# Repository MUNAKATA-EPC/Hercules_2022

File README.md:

# Hercules_2022

ヘラクレス2022シーズンのソースコード、基板データを公開しています。

詳しくはWikiを参照。

## 運用方針

- 大きな変更をするときはブランチを絶対に別途作成しましょう
- 小さな変更(スペルミスやコメント修正程度)ならどんどんmainブランチに突っ込んでもまあ構わないでしょう
- 余裕があったら変更した内容をコメントしてくれると助かります

## コードに関して

- 各プロジェクトフォルダの命名規則は「hogehoge(プロジェクト名)-teensy40(開発環境名)」となっていますが、一部試験用に作ったものに関しては、この命名規則が守られておりません...ごめんなさい。
- プロジェクトフォルダ内の「src」フォルダ内にmain.cpp(一部プロジェクトは名称が異なります)、「lib」フォルダ内に各種ライブラリ、「include」フォルダ内にサブプログラムが入っています。
- 一部PlatformIOからダウンロードしているライブラリが含まれているため、基本は「VSCode + PlatformIO」の組み合わせでご覧ください。

## 回路に関して

- 使用する設計ソフトにKiCad5と6が混在しています。
- ライブラリについてはLibraryフォルダを相対パスで参照しています。
- 発注は主にJLCPCBを使用します。

## 開発環境に関して

- VSCodeの拡張機能のPlatformIOを使用しTeensy 4.0とSeeeduino XIAOに書き込んでいます。
- 弊チームにはMacユーザーがいないため、Windows環境での開発を想定しております。Macをお使いの皆様、何か問題が生じても対応はできません。予めご了承ください。

## ライセンスに関して

- すべてのコード、基板データに関するライセンスはMITにしていますが、ライブラリ等のライセンスはそのライブラリごとのライセンスに従ってください。

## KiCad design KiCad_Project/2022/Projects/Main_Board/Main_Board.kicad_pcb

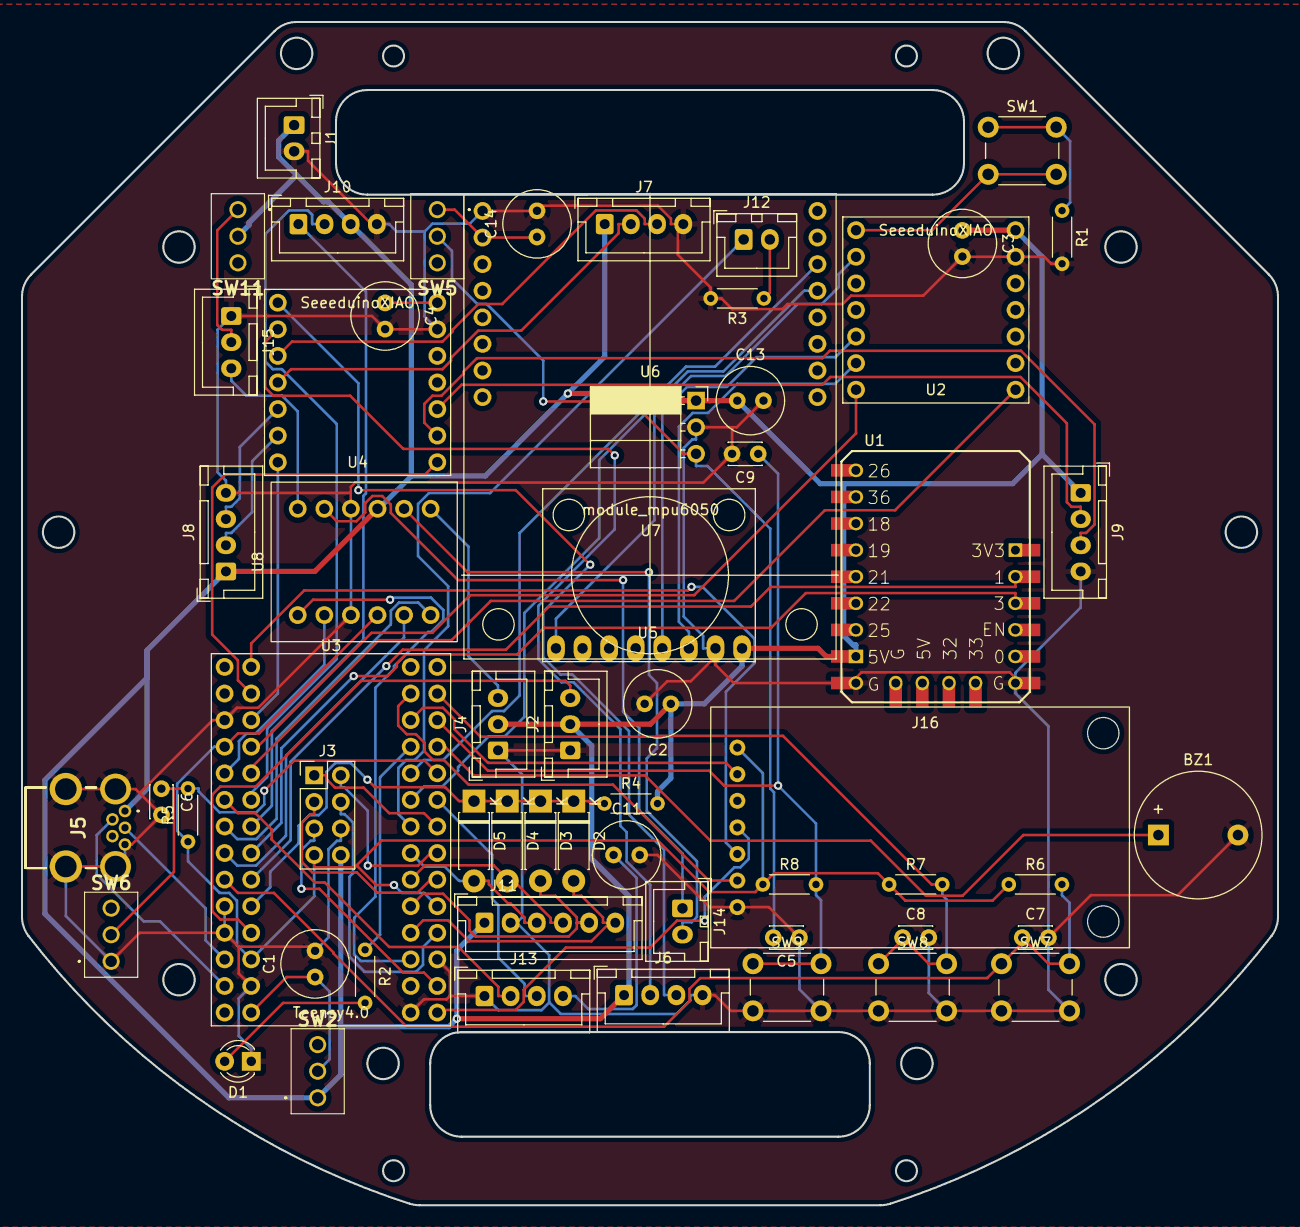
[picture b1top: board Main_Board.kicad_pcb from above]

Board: 2 copper layers, 120.0 x 113.0 mm, 58 parts (0 on the bottom side), 68 nets.

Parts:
BZ1: Buzzer; Buzzer_12x9.5RM7.6
C1, C2, C3, C4, C11, C13, C14: C_Small; C_Radial_D6.3mm_H11.0mm_P2.50mm
C5, C6, C7, C8, C9: C; C_Disc_D3.0mm_W2.0mm_P2.50mm
D1: LED; LED_D3.0mm_Clear
D2, D3, D4, D5: D; D_DO-41_SOD81_P7.62mm_Horizontal
J1, J12, J14: Conn_01x02; JST_XH_B2B-XH-A_1x02_P2.50mm_Vertical
J2, J4, J15: Conn_01x03; JST_XH_B3B-XH-A_1x03_P2.50mm_Vertical
J3: Conn_01x08; PinHeader_2x04_P2.54mm_Vertical
J5: USB_B_Micro; MUSB5BF01AS
J6, J7, J8, J9, J10, J13: Conn_01x04; JST_XH_B4B-XH-A_1x04_P2.50mm_Vertical
J11: Conn_01x06; JST_XH_B6B-XH-A_1x06_P2.50mm_Vertical
J16: Conn_01x07; LCD
R1, R2, R3, R4, R5, R6, R7, R8: R; R_Axial_DIN0204_L3.6mm_D1.6mm_P5.08mm_Horizontal
SW1, SW7, SW8, SW9: SW_Push; SW_PUSH_6mm_H5mm
SW2, SW5, SW11: SW_SPST; toggleswitch
SW6: SW_DIP_x01; toggleswitch
U1: Stamp_Pico; StampPico_template
U2, U4: SeeeduinoXIAO; seeeduinoXIAO
U3: Teensy4.0; Teensy
U5: OpenMV
U6: LF33_TO252; PinSocket_1x03_P2.54mm_Horizontal
U7: module_mpu6050; MPU6050
U8: Akizuki_Logiv_Level_converter; Akizuki_Logic_Level_converter

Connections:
+3V3: J3.7, J16.1, R5.1, R6.1, R7.1, R8.1, U3.31 (3V3), U8.9 (LV)
+5V: C2.1, C3.1, C13.1, J1.1, J2.2, J3.8, J4.2, J5.1 (VBUS), J6.1, J7.1, J8.1, J9.1, J10.3, J11.1, R4.2, SW2.1 (A), SW11.2 (B), U1.8 (5V), U2.14 (5V), U6.1 (VI), U7.1 (VCC), U8.4 (HV)
/Kicker: J12.1, U3.8 (6_OUT1D)
CS: J16.2, U3.12 (10_CS_MQSR)
GND: BZ1.2 (+), C1.2, C2.2, C3.2, C4.2, C5.1, C6.2, C7.2, C8.2, C9.2, C11.2, C13.2, C14.2, D1.1 (K), J1.2, J2.1, J3.6, J4.1, J5.5 (GND), J6.4, J7.4, J8.4, J9.4, J10.4, J11.2, J13.1, J15.1, J16.7, R1.2, R3.2, SW6.1, SW7.2, SW8.2, SW9.2, U1.9 (GND), U1.14 (GND), U2.13 (GND), U3.1 (GND), U4.13 (GND), U5.1 (GND), U6.2 (GND), U7.2 (GND), U8.3 (GND), U8.10 (GND)
Intterapt: D2.1 (K), D3.1 (K), D4.1 (K), D5.1 (K), R4.1, U3.29 (22_A8_CTX1)
MOSI: J16.6, U3.13 (11_MOSI_CTX1)
NeoPixel: U3.37 (26_A12_MOSI1), U8.7 (LV4)
unnamed: BZ1.1 (-), U3.44 (33_MCLK2)
unnamed: C1.1, SW2.2 (B), U3.33 (VIN)
unnamed: C4.1, U4.14 (5V)
unnamed: C5.2, SW5.2 (B), U6.3 (VO)
unnamed: C11.1, J13.4
unnamed: C14.1, SW5.1 (A), U5.2 (VIN)
unnamed: D1.2 (A), R2.2
unnamed: D2.2 (A), J11.6, U3.4 (2_OUT2)
unnamed: D3.2 (A), J11.5, U3.5 (3_LRCLK2)
unnamed: D4.2 (A), J11.4, U3.6 (4_BCLK2)
unnamed: D5.2 (A), J11.3, U3.7 (5_IN2)
unnamed: J2.3, U3.30 (23_A9_CRX1_MCLK1)
unnamed: J3.1, U3.52 (39_DAT2_TX5)
unnamed: J3.2, U3.51 (38_DAT3_RX5)
unnamed: J3.3, U3.50 (37_CMD_SCK2)
unnamed: J3.4, U3.48 (36_CLK_CS2)
unnamed: J3.5, U3.46 (35_DAT0_MOSI2)
unnamed: J4.3, U8.6 (HV4)
unnamed: J5.2 (D-), U3.53 (D-)
unnamed: J5.3 (D+), U3.54 (D+)
unnamed: J6.2, U4.2 (PA4_A1_D1)
unnamed: J6.3, U4.1 (PA02_A0_D0)
unnamed: J7.2, U4.4 (PA11_A3_D3)
unnamed: J7.3, U4.3 (PA10_A2_D2)
unnamed: J8.2, U4.6 (PA9_A5_D5_SCL)
unnamed: J8.3, U4.5 (PA8_A4_D4_SDA)
unnamed: J9.2, U4.10 (PA5_A9_D9_MISO)
unnamed: J9.3, U4.9 (PA7_A8_D8_SCK)
unnamed: J10.1, U3.26 (19_A5_SCL0)
unnamed: J10.2, U3.25 (18_A4_SDA0)
unnamed: J12.2, R3.1
unnamed: J14.1, U8.2 (HV2)
unnamed: J14.2, U8.5 (HV3)
unnamed: J15.2, SW11.1 (A)
unnamed: J15.3, U8.1 (HV1)
unnamed: R1.1, SW1.1
unnamed: R2.1, U3.11 (9_OUT1C)
unnamed: SW1.2, U2.1 (PA02_A0_D0)
unnamed: U2.2 (PA4_A1_D1), U7.8 (INT)
unnamed: U2.5 (PA8_A4_D4_SDA), U7.4 (SDA)
unnamed: U2.6 (PA9_A5_D5_SCL), U7.3 (SCL)
RS: J16.4, U3.45 (34_DAT1_MISO2)
RX2: U3.9 (7_RX2_OUT1A), U5.13 (P4)
RX3: U3.22 (15_A1_RX3_SPDIF_IN), U4.7 (PB08_A6_D6_TX)
RX4: U2.7 (PB08_A6_D6_TX), U3.23 (16_A2_RX4_SCL1)
RX5: U1.18 (G1), U3.28 (21_A7_RX5_BCLK1)
RX6: U3.36 (25_A11_RX6_SDA2), U8.8 (LV3)
RX7: J13.2, U3.39 (28_RX7)
SCK: J16.5, U3.20 (13_SCK_CRX1_LED)
SW1: C7.1, R6.2, SW7.1, U3.38 (27_A13_SCK1)
SW2: C8.1, R7.2, SW8.1, U3.41 (30_CRX3)
SW3: C9.1, R8.2, SW9.1, U3.43 (32_OUT1B)
SW4: C6.1, R5.2, SW6.2, U3.42 (31_CTX3)
TX1: U3.3 (1_TX1_CTX2_MISO1), U8.12 (LV1)
TX2: U3.10 (8_TX2_IN1), U5.14 (P5)
TX3: U3.21 (14_A0_TX3_SPDIF_OUT), U4.8 (PB09_A7_D7_RX)
TX4: U2.8 (PB09_A7_D7_RX), U3.24 (17_A3_TX4_SDA1)
TX5: U1.17 (G3), U3.27 (20_A6_TX5_LRCLK1)
TX6: U3.35 (24_A10_TX6_SCL2), U8.11 (LV2)
TX7: J13.3, U3.40 (29_TX7)

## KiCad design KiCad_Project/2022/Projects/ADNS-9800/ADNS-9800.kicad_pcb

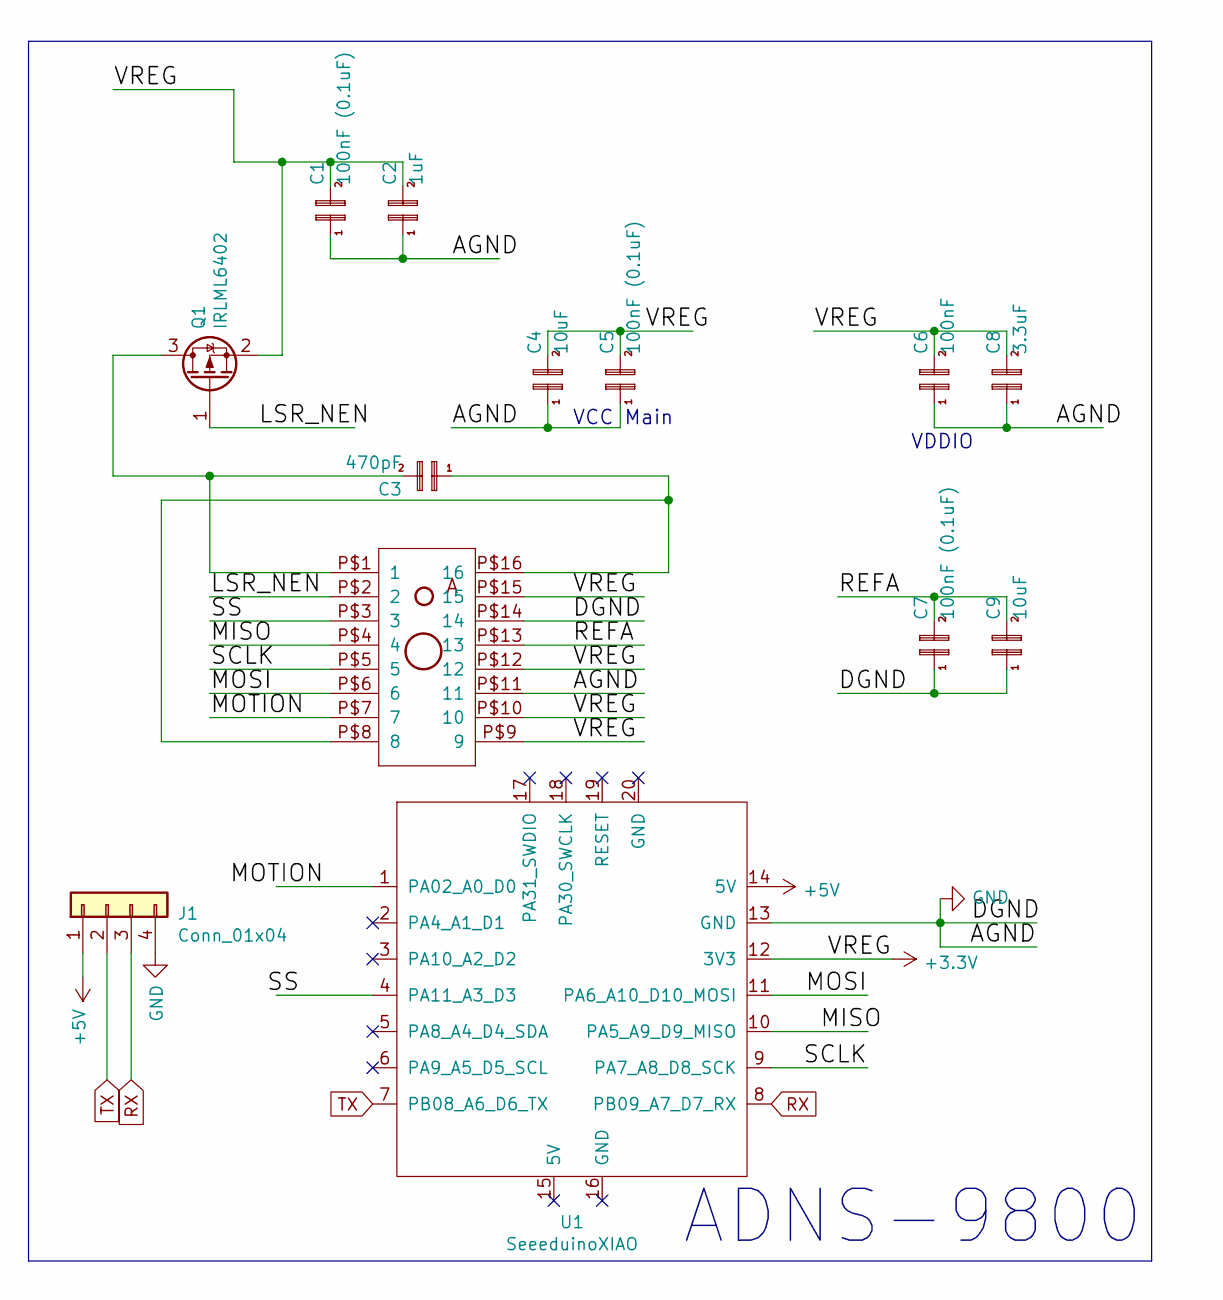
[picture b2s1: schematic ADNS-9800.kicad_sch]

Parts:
C1, C5, C7: 100nF (0.1uF); C_0603_1608Metric_Pad1.08x0.95mm_HandSolder
C2: 1uF; C_0603_1608Metric_Pad1.08x0.95mm_HandSolder
C3: 470pF; C_0603_1608Metric_Pad1.08x0.95mm_HandSolder
C4, C9: 10uF; C_0603_1608Metric_Pad1.08x0.95mm_HandSolder
C6: 100nF; C_0603_1608Metric_Pad1.08x0.95mm_HandSolder
C8: 3.3uF; C_0603_1608Metric_Pad1.08x0.95mm_HandSolder
J1: Conn_01x04; JST_XH_S4B-XH-A_1x04_P2.50mm_Horizontal
Q1: IRLML6402; SOT-23
U1: SeeeduinoXIAO; Seeeduino XIAO-MOUDLE14P-2.54-21X17.8MM
U$1: AVAGO_ADNS-9500

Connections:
+3V3: C1.2, C2.2, C4.2, C5.2, C6.2, C8.2, Q1.2 (S), U1.12 (3V3), U$1.P$9 (9), U$1.P$10 (10), U$1.P$12 (12), U$1.P$15 (15)
+5V: J1.1, U1.14 (5V)
/LSR_NEN: Q1.1 (G), U$1.P$2 (2)
/MISO: U1.10 (PA5_A9_D9_MISO), U$1.P$4 (4)
/MOSI: U1.11 (PA6_A10_D10_MOSI), U$1.P$6 (6)
/MOTION: U1.1 (PA02_A0_D0), U$1.P$7 (7)
/REFA: C7.2, C9.2, U$1.P$13 (13)
/SCLK: U1.9 (PA7_A8_D8_SCK), U$1.P$5 (5)
/SS: U1.4 (PA11_A3_D3), U$1.P$3 (3)
GND: C1.1, C2.1, C4.1, C5.1, C6.1, C7.1, C8.1, C9.1, J1.4, U1.13 (GND), U$1.P$11 (11), U$1.P$14 (14)
unnamed: C3.1, U$1.P$8 (8), U$1.P$16 (16)
unnamed: C3.2, Q1.3 (D), U$1.P$1 (1)
RX: J1.3, U1.8 (PB09_A7_D7_RX)
TX: J1.2, U1.7 (PB08_A6_D6_TX)

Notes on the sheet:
VCC Main
ADNS-9800
VDDIO

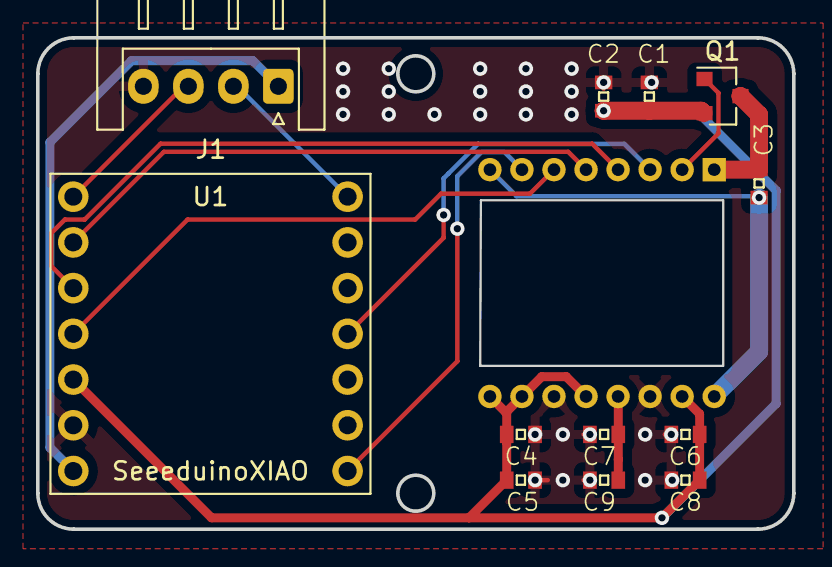
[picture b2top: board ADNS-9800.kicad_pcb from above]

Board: 2 copper layers, 42.0 x 27.3 mm, 13 parts (0 on the bottom side), 14 nets.

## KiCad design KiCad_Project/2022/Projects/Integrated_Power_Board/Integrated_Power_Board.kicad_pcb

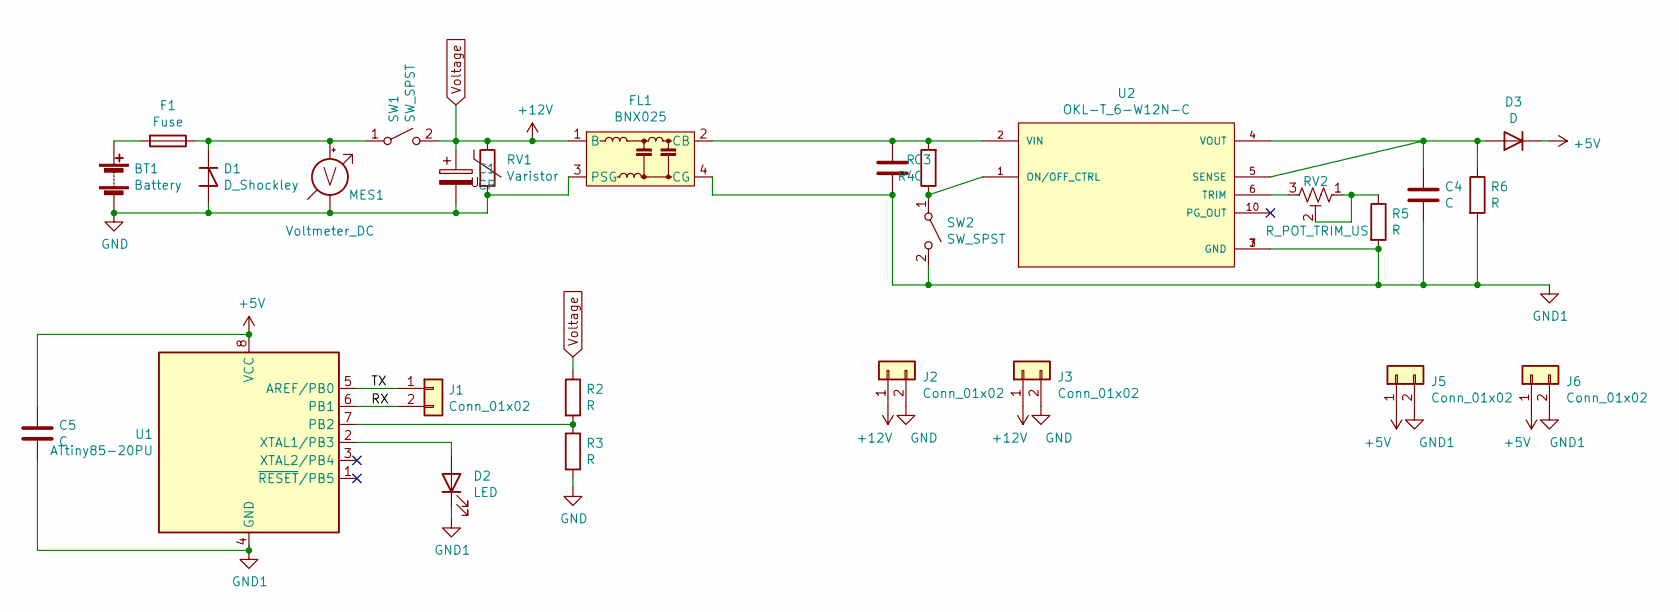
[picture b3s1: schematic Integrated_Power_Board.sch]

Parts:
BT1: Battery; JST_VH_B2P-VH-B_1x02_P3.96mm_Vertical
C1: CP; C_Radial_D16.0mm_H25.0mm_P7.50mm
C3, C4: C; C_Disc_D4.3mm_W1.9mm_P5.00mm
C5: C; C_Disc_D3.0mm_W1.6mm_P2.50mm
D1: D_Shockley; D_DO-201AD_P12.70mm_Horizontal
D2: LED; LED_D3.0mm_Clear
D3: D; D_DO-41_SOD81_P7.62mm_Horizontal
F1: Fuse; fuse_socket
FL1: BNX025; FIL_BNX016-01
J1, J2, J3, J5, J6: Conn_01x02; JST_XH_B2B-XH-A_1x02_P2.50mm_Vertical
MES1: Voltmeter_DC; voltage_counter
R2, R3, R4, R5, R6: R; R_Axial_DIN0207_L6.3mm_D2.5mm_P7.62mm_Horizontal
RV1: Varistor; RV_Disc_D9mm_W3.3mm_P5mm
RV2: R_POT_TRIM_US; Potentiometer_Bourns_3296W_Vertical
SW1: SW_SPST; DS-850k
SW2: SW_SPST; toggleswitch
U1: ATtiny85-20PU; DIP-8_W7.62mm
U2: OKL-T_6-W12N-C; DCDC-murata-6A

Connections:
+5V: C5.1, D3.1 (K), J5.1, J6.1, U1.8 (VCC)
/RX: J1.2, U1.6 (PB1)
/TX: J1.1, U1.5 (AREF/PB0)
GND: BT1.1 (-), C1.2, D1.2 (A), FL1.3 (PSG), J2.2, J3.2, MES1.1 (-), R3.2, RV1.2
GND1: C3.2, C4.2, C5.2, D2.1 (K), FL1.4 (CG), J5.2, J6.2, R5.2, R6.2, SW2.2 (B), U1.4 (GND), U2.3 (GND), U2.7 (GND)
unnamed: BT1.2 (+), F1.2
unnamed: C3.1, FL1.2 (CB), R4.2, U2.2 (VIN)
unnamed: C4.1, D3.2 (A), R6.1, U2.4 (VOUT), U2.5 (SENSE)
unnamed: D1.1 (K), F1.1, MES1.2 (+), SW1.1 (A)
unnamed: D2.2 (A), U1.2 (XTAL1/PB3)
unnamed: R2.2, R3.1, U1.7 (PB2)
unnamed: R4.1, SW2.1 (A), U2.1 (ON/OFF_CTRL)
unnamed: R5.1, RV2.1, RV2.2
unnamed: RV2.3, U2.6 (TRIM)
Voltage: C1.1, FL1.1 (B), J2.1, J3.1, R2.1, RV1.1, SW1.2 (B)

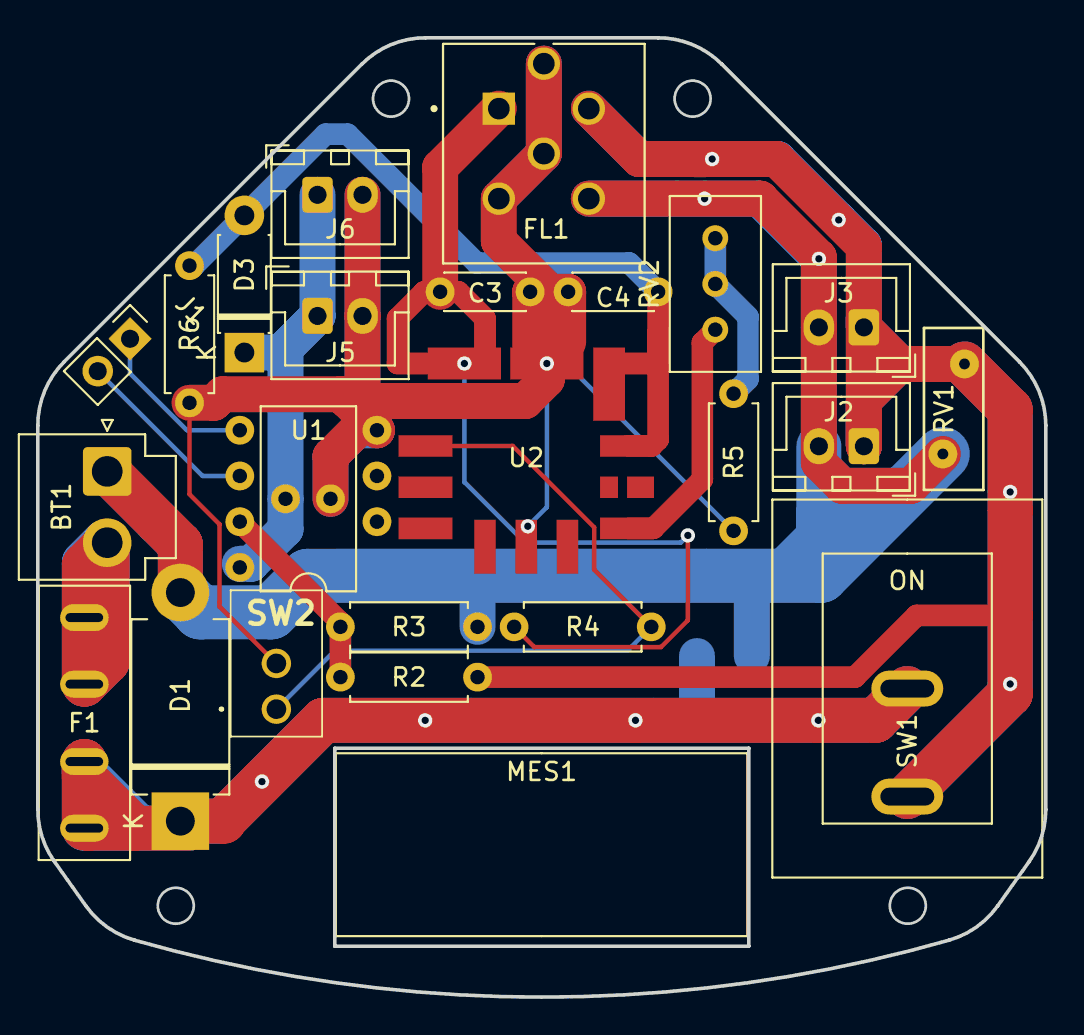
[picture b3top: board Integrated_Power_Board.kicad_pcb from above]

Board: 2 copper layers, 56.0 x 53.3 mm, 25 parts (1 on the bottom side), 14 nets.

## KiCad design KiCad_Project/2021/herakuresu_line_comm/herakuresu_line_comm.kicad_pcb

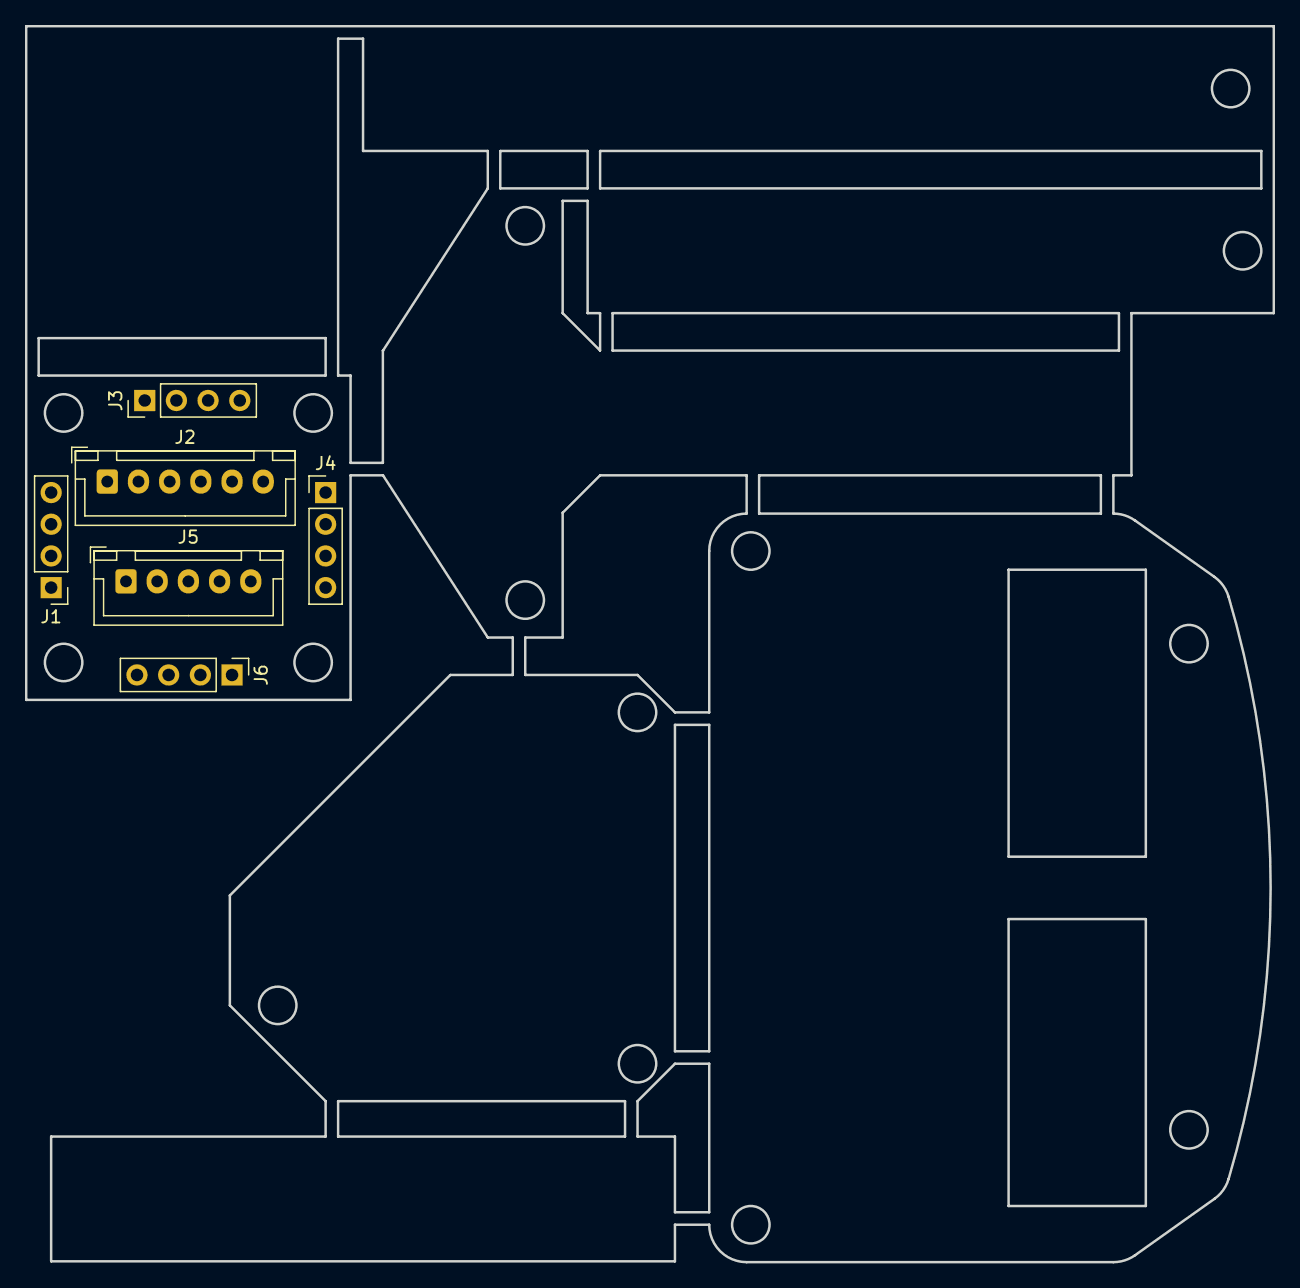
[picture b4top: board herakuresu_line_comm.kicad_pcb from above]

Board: 2 copper layers, 100.0 x 99.1 mm, 6 parts (0 on the bottom side), 10 nets, no tracks yet.

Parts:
J1, J3, J4, J6: Conn_01x04; PinHeader_1x04_P2.54mm_Vertical
J2: Conn_01x06; JST_XH_B6B-XH-A_1x06_P2.50mm_Vertical
J5: Conn_01x05; JST_XH_B5B-XH-A_1x05_P2.50mm_Vertical

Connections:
unnamed: J1.1, J5.1
unnamed: J1.2, J2.2, J3.2, J4.2, J6.2
unnamed: J1.3, J2.1, J3.3, J4.3, J5.5, J6.3
unnamed: J1.4, J2.3
unnamed: J2.4, J3.4
unnamed: J2.5, J4.4
unnamed: J2.6, J6.4
unnamed: J3.1, J5.2
unnamed: J4.1, J5.3
unnamed: J5.4, J6.1

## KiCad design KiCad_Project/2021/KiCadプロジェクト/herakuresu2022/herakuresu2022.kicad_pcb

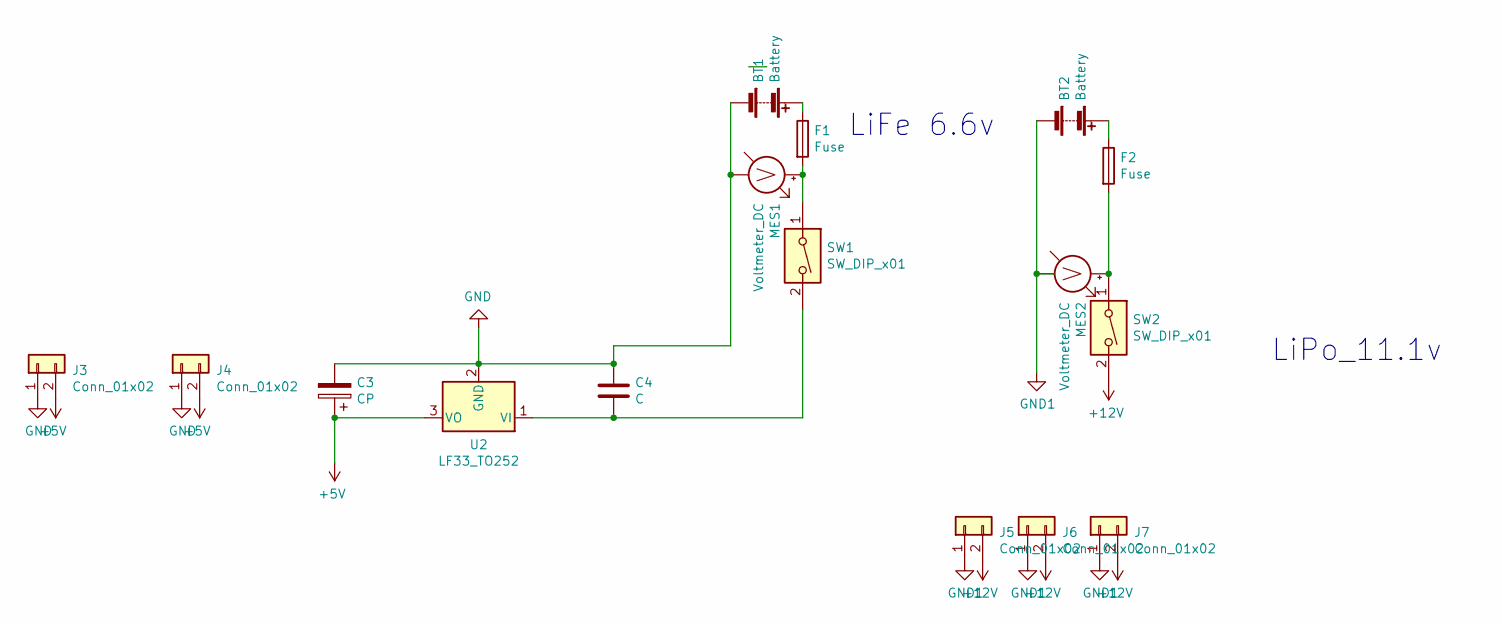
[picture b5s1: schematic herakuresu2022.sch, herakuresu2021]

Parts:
BT1: Battery; JST_XH_B2B-XH-A_1x02_P2.50mm_Vertical
BT2: Battery; JST_VH_B2P-VH-FB-B_1x02_P3.96mm_Vertical
C3: CP; C_Radial_D6.3mm_H11.0mm_P2.50mm
C4: C; C_Disc_D3.0mm_W2.0mm_P2.50mm
F1, F2: Fuse; fuse_socket
J3, J4, J5, J6, J7: Conn_01x02; JST_XH_B2B-XH-A_1x02_P2.50mm_Vertical
MES1, MES2: Voltmeter_DC; voltage_counter
SW1, SW2: SW_DIP_x01; 2MS1T2B4M2QES
U2: LF33_TO252; TO-262-3_Vertical

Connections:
+5V: C3.1, J3.2, J4.2, U2.3 (VO)
+12V: J5.2, J6.2, J7.2, SW2.2
GND: BT1.1 (-), C3.2, C4.1, J3.1, J4.1, MES1.1 (-), U2.2 (GND)
GND1: BT2.1 (-), J5.1, J6.1, J7.1, MES2.1 (-)
unnamed: BT1.2 (+), F1.1
unnamed: BT2.2 (+), F2.1
unnamed: C4.2, SW1.2, U2.1 (VI)
unnamed: F1.2, MES1.2 (+), SW1.1
unnamed: F2.2, MES2.2 (+), SW2.1

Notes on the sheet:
LiFe 6.6v
LiPo_11.1v

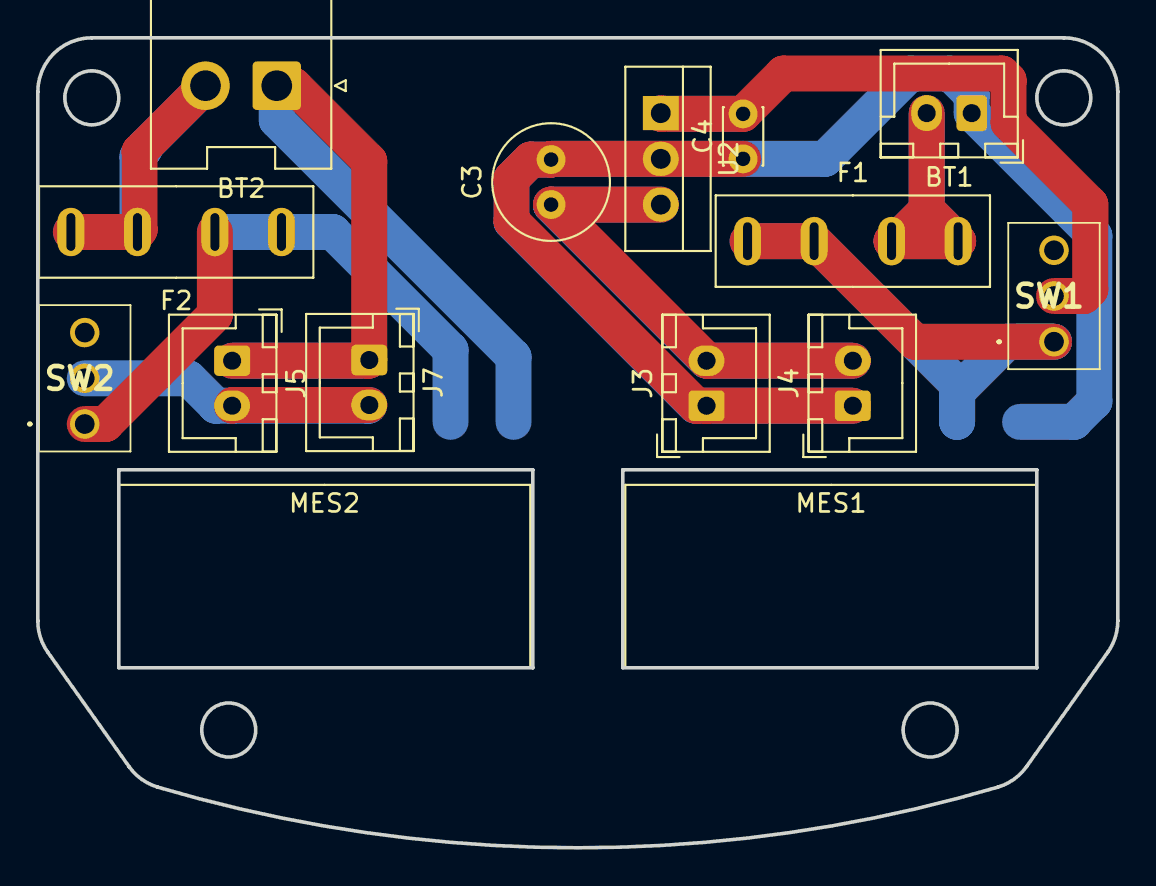
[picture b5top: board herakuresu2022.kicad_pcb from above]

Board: 2 copper layers, 60.0 x 45.0 mm, 15 parts (0 on the bottom side), 9 nets.

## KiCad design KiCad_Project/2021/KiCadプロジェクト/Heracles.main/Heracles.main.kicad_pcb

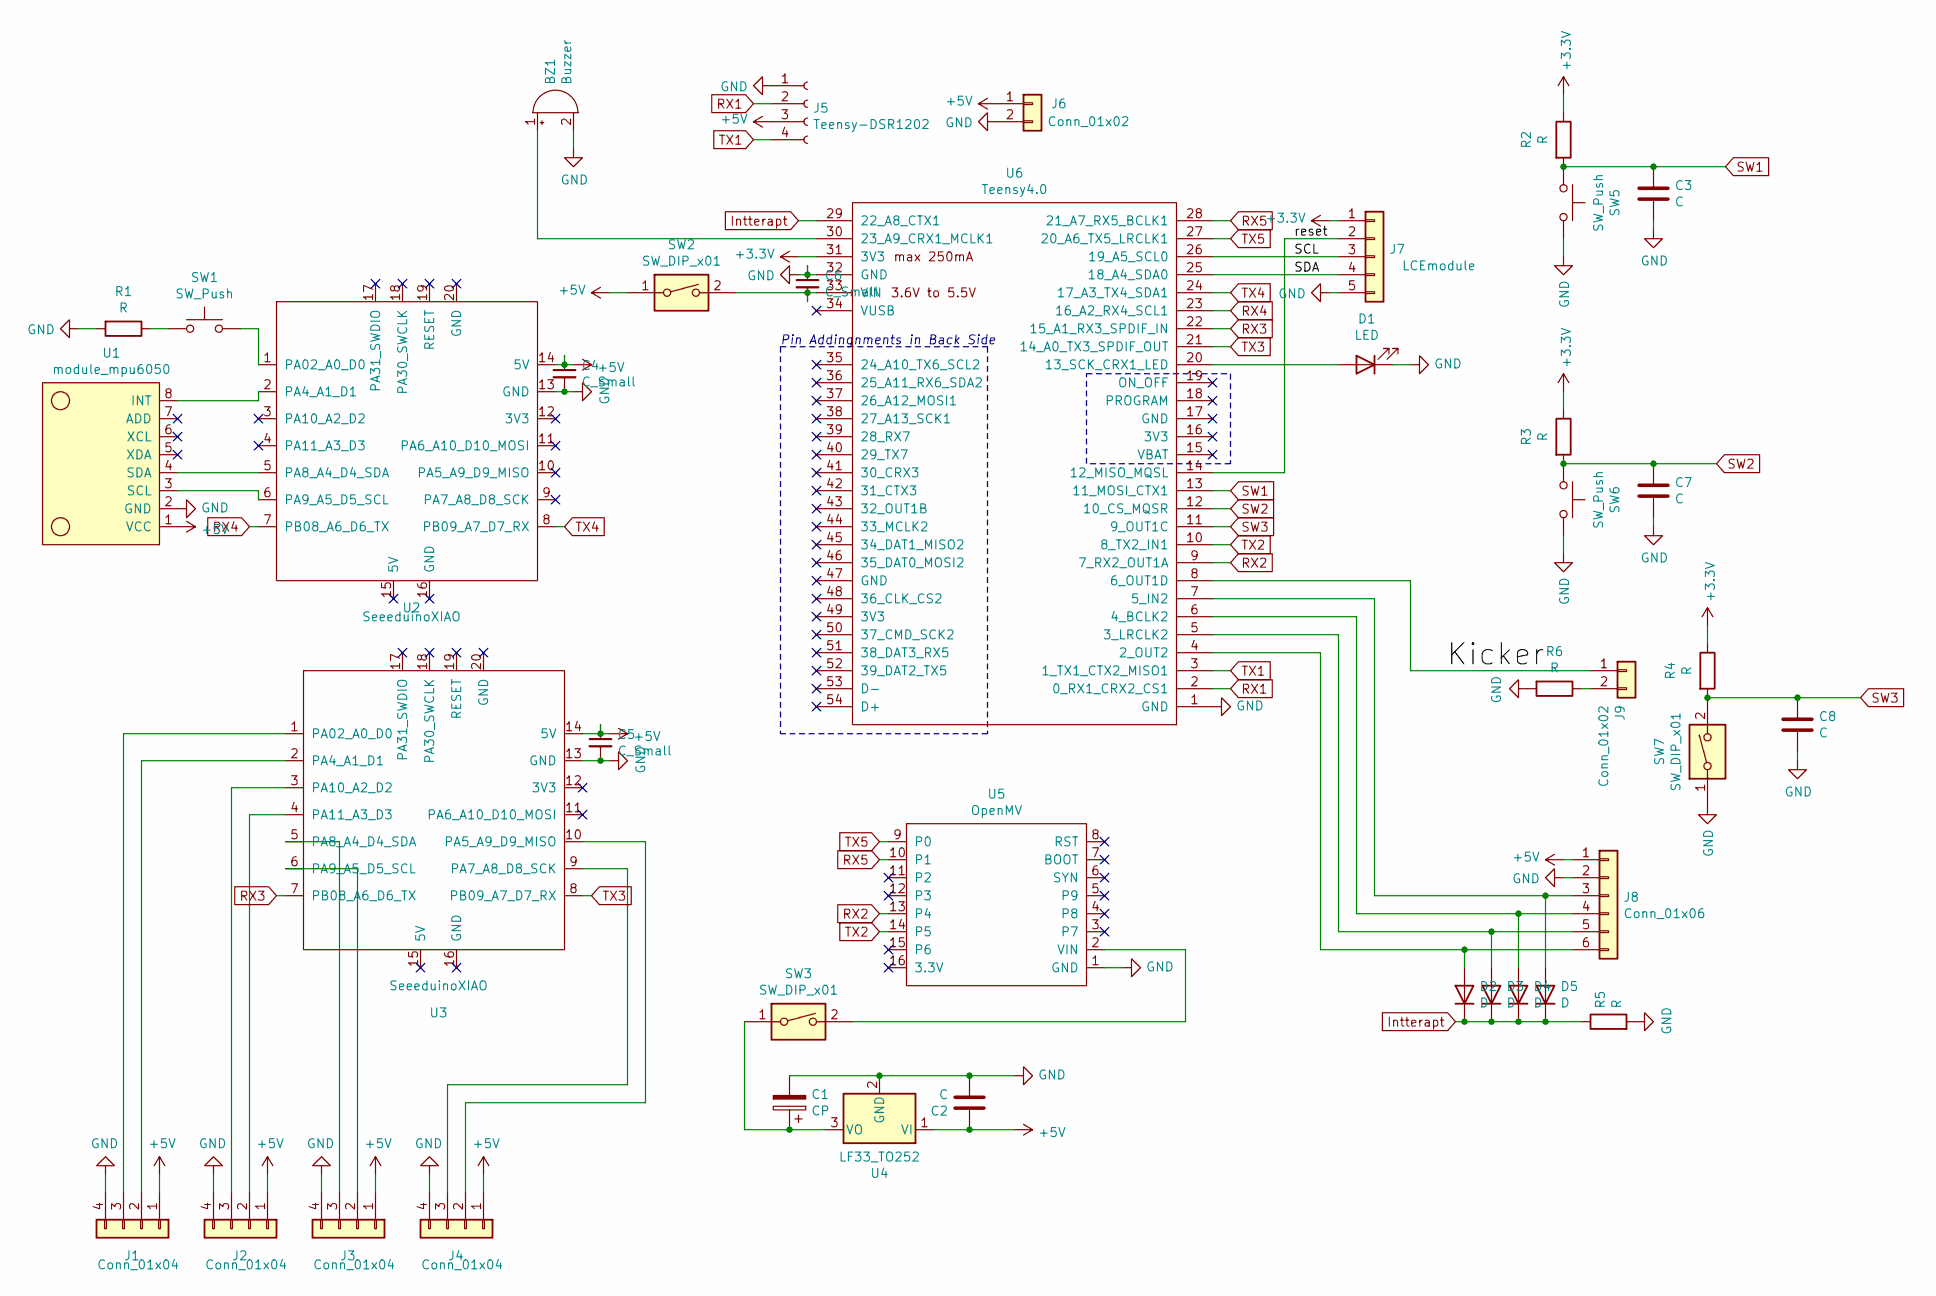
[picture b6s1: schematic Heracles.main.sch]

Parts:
BZ1: Buzzer; Buzzer_15x7.5RM7.6
C1: CP; C_Radial_D6.3mm_H11.0mm_P2.50mm
C2, C3, C7, C8: C; C_Disc_D3.0mm_W2.0mm_P2.50mm
C4, C5, C6: C_Small; C_Disc_D3.0mm_W2.0mm_P2.50mm
D1: LED; LED_D3.0mm_Clear
D2, D3, D4, D5: D; D_DO-41_SOD81_P7.62mm_Horizontal
J1, J2, J3, J4: Conn_01x04; JST_XH_B4B-XH-A_1x04_P2.50mm_Vertical
J5: Teensy-DSR1202; JST_XH_B4B-XH-A_1x04_P2.50mm_Vertical
J6, J9: Conn_01x02; JST_XH_B2B-XH-A_1x02_P2.50mm_Vertical
J7: LCEmodule; LCDmodule
J8: Conn_01x06; JST_XH_B6B-XH-A_1x06_P2.50mm_Vertical
R1, R2, R3, R4, R5, R6: R; R_Axial_DIN0204_L3.6mm_D1.6mm_P5.08mm_Horizontal
SW1, SW5: SW_Push; SW_PUSH_6mm_H5mm
SW2, SW3, SW7: SW_DIP_x01; toggleswitch
SW6: SW_Push; PushSwitch
U1: module_mpu6050; MPU6050
U2, U3: SeeeduinoXIAO; seeeduinoXIAO
U4: LF33_TO252; TO-252-2
U5: OpenMV
U6: Teensy4.0; Teensy

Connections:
+3V3: J7.1, R2.1, R3.1, R4.1, U6.31 (3V3)
+5V: C2.1, C4.1, C5.1, J1.1, J2.1, J3.1, J4.1, J5.3, J6.1, J8.1, SW2.1, U1.1 (VCC), U2.14 (5V), U3.14 (5V), U4.1 (VI)
/Kicker: J9.1, U6.8 (6_OUT1D)
/SCL: J7.3, U6.26 (19_A5_SCL0)
/SDA: J7.4, U6.25 (18_A4_SDA0)
/reset: J7.2, U6.14 (12_MISO_MQSL)
GND: BZ1.2 (+), C1.2, C2.2, C3.2, C4.2, C5.2, C6.1, C7.2, C8.2, D1.1 (K), J1.4, J2.4, J3.4, J4.4, J5.1, J6.2, J7.5, J8.2, R1.2, R5.2, R6.2, SW5.2, SW6.2, SW7.1, U1.2 (GND), U2.13 (GND), U3.13 (GND), U4.2 (GND), U5.1 (GND), U6.1 (GND), U6.32 (GND)
Intterapt: D2.1 (K), D3.1 (K), D4.1 (K), D5.1 (K), R5.1, U6.29 (22_A8_CTX1)
unnamed: BZ1.1 (-), U6.30 (23_A9_CRX1_MCLK1)
unnamed: C1.1, SW3.1, U4.3 (VO)
unnamed: C6.2, SW2.2, U6.33 (VIN)
unnamed: D1.2 (A), U6.20 (13_SCK_CRX1_LED)
unnamed: D2.2 (A), J8.6, U6.4 (2_OUT2)
unnamed: D3.2 (A), J8.5, U6.5 (3_LRCLK2)
unnamed: D4.2 (A), J8.4, U6.6 (4_BCLK2)
unnamed: D5.2 (A), J8.3, U6.7 (5_IN2)
unnamed: J1.2, U3.2 (PA4_A1_D1)
unnamed: J1.3, U3.1 (PA02_A0_D0)
unnamed: J2.2, U3.4 (PA11_A3_D3)
unnamed: J2.3, U3.3 (PA10_A2_D2)
unnamed: J3.2, U3.6 (PA9_A5_D5_SCL)
unnamed: J3.3, U3.5 (PA8_A4_D4_SDA)
unnamed: J4.2, U3.10 (PA5_A9_D9_MISO)
unnamed: J4.3, U3.9 (PA7_A8_D8_SCK)
unnamed: J9.2, R6.1
unnamed: R1.1, SW1.1
unnamed: SW1.2, U2.1 (PA02_A0_D0)
unnamed: SW3.2, U5.2 (VIN)
unnamed: U1.3 (SCL), U2.6 (PA9_A5_D5_SCL)
unnamed: U1.4 (SDA), U2.5 (PA8_A4_D4_SDA)
unnamed: U1.8 (INT), U2.2 (PA4_A1_D1)
RX1: J5.2, U6.2 (0_RX1_CRX2_CS1)
RX2: U5.13 (P4), U6.9 (7_RX2_OUT1A)
RX3: U3.7 (PB08_A6_D6_TX), U6.22 (15_A1_RX3_SPDIF_IN)
RX4: U2.7 (PB08_A6_D6_TX), U6.23 (16_A2_RX4_SCL1)
RX5: U5.10 (P1), U6.28 (21_A7_RX5_BCLK1)
SW1: C3.1, R2.2, SW5.1, U6.13 (11_MOSI_CTX1)
SW2: C7.1, R3.2, SW6.1, U6.12 (10_CS_MQSR)
SW3: C8.1, R4.2, SW7.2, U6.11 (9_OUT1C)
TX1: J5.4, U6.3 (1_TX1_CTX2_MISO1)
TX2: U5.14 (P5), U6.10 (8_TX2_IN1)
TX3: U3.8 (PB09_A7_D7_RX), U6.21 (14_A0_TX3_SPDIF_OUT)
TX4: U2.8 (PB09_A7_D7_RX), U6.24 (17_A3_TX4_SDA1)
TX5: U5.9 (P0), U6.27 (20_A6_TX5_LRCLK1)

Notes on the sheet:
Pin Addingnments in Back Side

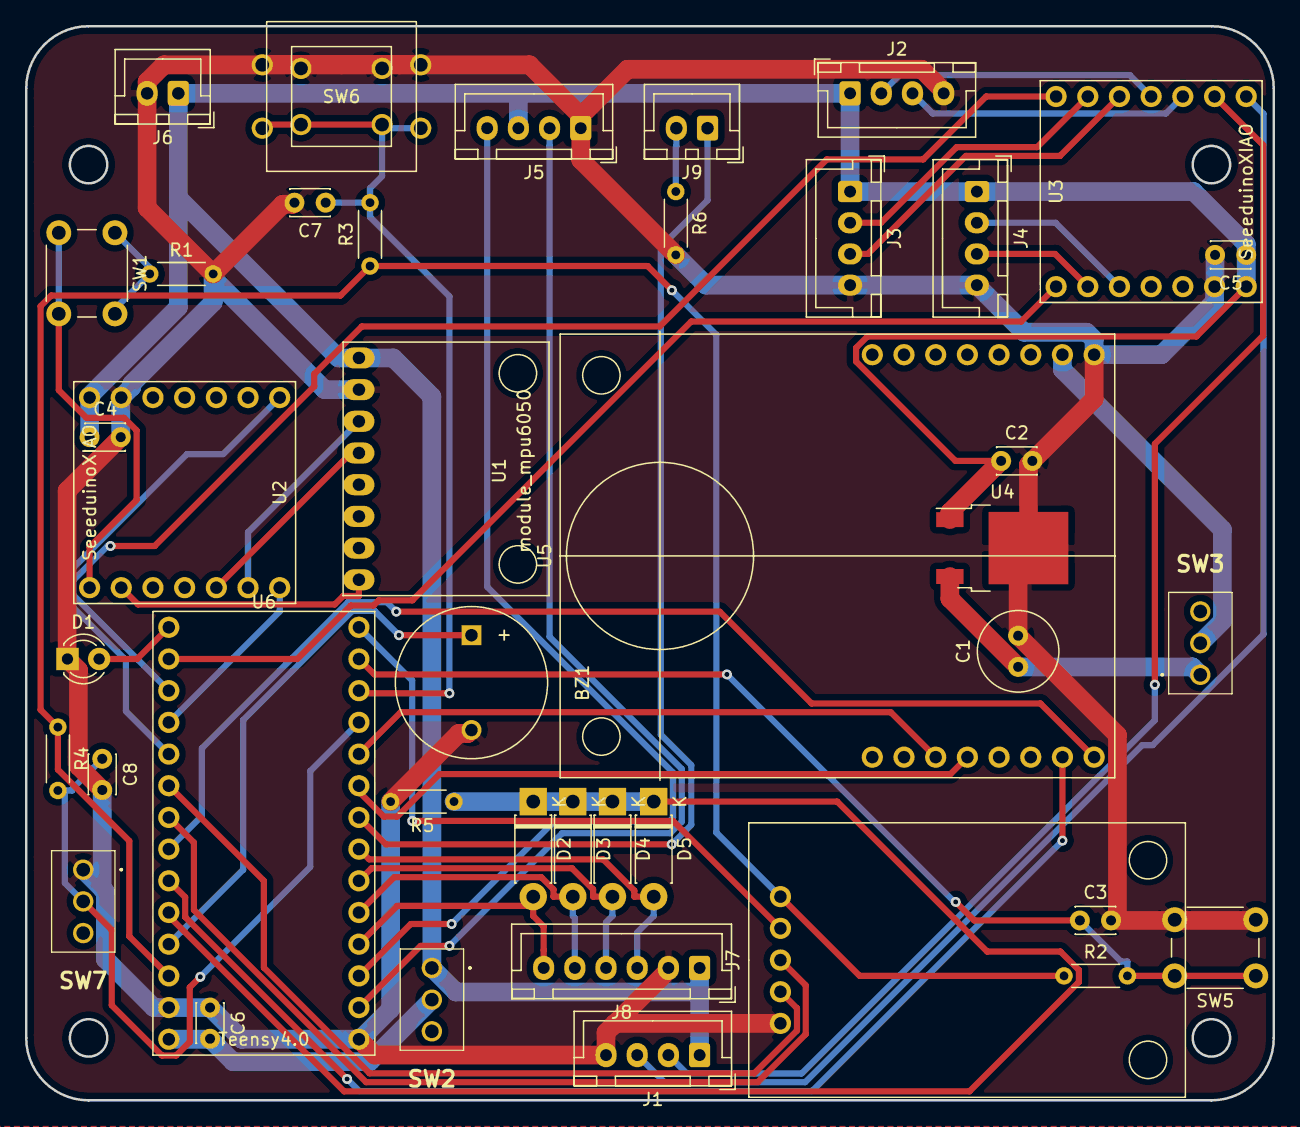
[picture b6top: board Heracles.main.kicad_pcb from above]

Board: 2 copper layers, 100.0 x 86.1 mm, 41 parts (0 on the bottom side), 44 nets.

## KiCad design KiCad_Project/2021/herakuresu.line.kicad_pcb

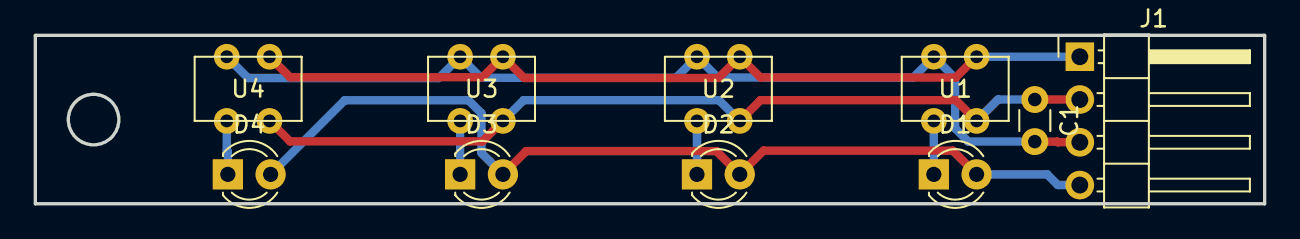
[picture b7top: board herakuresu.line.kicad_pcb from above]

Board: 2 copper layers, 73.0 x 10.0 mm, 10 parts (0 on the bottom side), 8 nets.

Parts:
C1: C; C_Disc_D3.0mm_W1.6mm_P2.50mm
D1, D2, D3, D4: LED; LED_D3.0mm_Clear
J1: Conn_01x04_Female; PinHeader_1x04_P2.54mm_Horizontal
U1, U2, U3, U4: S4282; S428

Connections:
+5V: C1.1, J1.2, U1.2, U2.2, U3.2, U4.2
GND: C1.2, J1.3, U1.4, U2.4, U3.4, U4.4
LED: D1.2, D2.2, D3.2, D4.2, J1.4
unnamed: D1.1, U1.1
unnamed: D2.1, U2.1
unnamed: D3.1, U3.1
unnamed: D4.1, U4.1
Vout: J1.1, U1.3, U2.3, U3.3, U4.3

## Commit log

2021-12-26 Create LICENSE
2021-12-26 ふじたきよゆきが編集しました
2021-12-26 メッセージ削除
2021-12-26 スペースが増えたよ！(見づらくて草)
2021-12-26 編集してみました
2021-12-27 説明を増やしました
2021-12-27 作りかけです
2021-12-27 あとは各種モーターの値を設定してあげてください
2021-12-27 表示内容を変更しました
2021-12-27 IMUの値反転とCAM情報取得処理を追加
2021-12-27 CAMとPID制御用の変数を追加
2021-12-27 ラインやカメラ角度などのおおまかな骨組みを作成
2021-12-27 test.cppなんてなかった。いいね？
2021-12-27 テストコメントの削除
2021-12-27 スペースが減ったよ
2021-12-27 PID設定してね
2021-12-27 色々調整入れました
2021-12-27 なんちゃってクラス導入
2021-12-27 ちょっとずつ変わったで
2021-12-28 PID制御実装
2021-12-28 モーター限界値設定をMotor各関数内で行うようにしました
2021-12-28 LCD切り替えスイッチを押すと、プログラムの実行状態が必ず解除されるようになりました
2021-12-28 MD準備開始位置の変更と、OpenMVとの通信を行えるようにしました
2021-12-28 USBシリアル通信の速度を115200bpsに統一しました
2021-12-30 定位置用の情報は送らないようにしました。そして、送信が完了するまで待機するようになります。
2021-12-30 クラスにまとめました
2022-01-02 KiCadプロジェクトファイルの作成
2022-01-05 自分好みに変えました
2022-01-05 コメント位置が変わりました
2022-01-05 私好みになりました
2022-01-05 PIDパラメータ値をここで変えれるようにしました
2022-01-05 誤動作防止処理を追加しました
2022-01-05 クラスの表記がまとまったり、ゲイン値が消えたり
2022-01-05 ライブラリとヘッダファイルで表記を変えました
2022-01-06 コードの最適化
2022-01-06 コードの最適化(変数被りの除去)
2022-01-06 変数被り防止
2022-01-06 変数被り防止とメモリ使用量削減
2022-01-06 ピン番号の修正
2022-01-06 Source Treeテストコメントの追加
2022-01-06 テストコメント削除
2022-01-07 トグルスイッチの役割をモード固定的なものへと変更しました
2022-01-07 モーターモードに姿勢制御を実装
2022-01-07 操作量の上限値、下限値の見直し
2022-01-07 操作量上限値とモーター速度がパラメータ設定から変更可能になりました
2022-01-07 モーター速度をパラメータに置き換えました
2022-01-07 モーター速度限界値をパラメータから調整できるようになりました
2022-01-08 PID制御を一時的に外してます
2022-01-08 タイプミス修正
2022-01-08 パラメータを変数化
2022-01-08 PID制御の読み込みを一時的に外しました
2022-01-13 方向判定の変数化
2022-01-13 LCD表示バグの修正
2022-01-13 方向判定の仕様変更
2022-01-15 出力バランス調整
2022-01-15 関数呼び出し時にどの値が何なのかわかるようにコメントを追加
2022-01-16 IMU閾値を読み込み専用に変更
2022-01-18 アナログ出力分解能を変更
2022-01-19 開発間に合わないんで
2022-01-19 ミス修正とか色々
2022-01-19 走り抜けるぜッ！最後まで
2022-01-19 gotoの削除
2022-01-19 処理の仕様変更
2022-01-19 変数の追加と削除
2022-01-19 loop関数内は全て条件分岐での動作に変更
2022-01-20 回路関係のファイルをGitにまとめました
    発注ファイルとDFXでごちゃごちゃしてるのはすいません
2022-01-20 統合電源基板
2022-01-21 処理の若干の変更
2022-01-21 色々微調整
2022-01-21 nakamoto的メインプログラム
2022-01-21 ライブラリの追加
2022-01-21 EMI対策とDCDCの周辺設計
    過電流保護機能・加熱保護機能付き
    可変抵抗で出力の変更可能
2022-01-21 回路図の完成
2022-01-22 仕様変更
2022-01-22 ラインセンサをデジタルで読むように変更
2022-01-22 IMUの範囲調整
2022-01-22 メインプログラム(仮)
2022-01-22 RCAPで開発した遺産たち
2022-01-22 MPU遺産削除
2022-01-22 MPU6050用のXiaoプログラム
2022-01-22 定位置が動作しないおそれのある不具合を修正
2022-01-22 OpenMVプログラムの移植
2022-01-22 定位置の変更
2022-01-23 九州ブロック 本番調整
2022-01-23 カメラ通信の安定化
2022-01-23 コネクタの逆差し対策
    ショットキーバリスタダイオードでDCDCよりも前に素早く短絡させます
2022-01-24 プチ変更
2022-01-27 九州ブロックでのやつ
2022-01-29 PID制御のリベンジとクラスの追加
2022-01-29 ライブラリを初期化
2022-01-29 このリポジトリのライセンスについて
2022-01-30 Update LICENSE
2022-02-01 電源統合基板の進捗
2022-02-05 Kicadプロジェクトの整理
    ファイルについて
    各基板のプロジェクト・ライブラリ・PDF・DXF・自動配線用・発注ファイル
    に分けました。
    またライブラリのインポートに際してプロフェクトからの相対パスに変更したため環境を変更しても編集することができます。
2022-02-05 keep
2022-02-05 環境設定
2022-02-07 電源系の設計の完了
    ATtinyを使って電圧を測定してシリアルでメインマイコンに送信します
    レベル変換についてはまだ考えてない
2022-02-09 部品の配置
2022-02-10 ビアを追加してノイズ対策
2022-02-12 統合電源基板の設計の完了
2022-02-13 設計図資料の更新と発注用ファイルの作成
2022-02-15 ごちゃごちゃ感が若干改善された
2022-02-15 回り込みの関数化
2022-02-15 積分値の初期化範囲の設定
2022-02-15 発注ファイルの設定の変更
2022-02-17 視認性が向上？
2022-02-17 データの受信仕様変更
2022-02-19 メンテナンス性の向上
2022-02-19 回り込みの仕様変更とか
2022-02-24 マウスセンサの設計の完了
    ADNS－9800使用
    SeeeduinoXIAOを用いてUARTでメインマイコンと通信
2022-03-01 メインボードの開発
2022-03-01 READMEの編集
2022-03-10 Startupをmain内に移動
2022-03-14 Teensy4.0_Breakout_Board
2022-03-18 メインボードの進捗
2022-03-19 MPU6050ジャイロ仕様変更
2022-03-19 VSCode拡張機能関係の追加
2022-03-19 PID制御をごにょごにょしたやつ
2022-03-19 PID周りをごにょごにょ
2022-03-19 変更点のコミット
2022-03-21 ライブラリの参照問題？
2022-03-22 マウス基板の改良
2022-03-22 バックアップ
2022-03-22 ライブラリの編集
2022-03-22 ライブラリの参照問題
2022-03-22 徹夜の進捗、朝マック食べに行きます
2022-03-23 フットプリントライブラリの編集
2022-03-25 フットプリントの割り当てまで終わった
2022-03-26 DXFの出力
2022-03-27 PID制御のある程度の仕様固め
2022-03-27 switch caseに置き換え
2022-03-27 回り込み調整段階
2022-03-27 最終的な基板の完成
2022-03-28 レジストを抜いて文字とURLを記入
2022-03-28 基板発注が完了しました
    ちなみに合計金額8000円でした
2022-03-29 PDFの作成
2022-04-02 クソ雑魚PD制御
2022-04-02 フィールドの緑色を使うようになりました
2022-04-02 フィールドの緑色をカラートラッキングできるようになりました
2022-04-02 変数名の誤り訂正
2022-04-02 親愛なるロボカッパーたちへ ゴールのトラッキング機能も仮実装されました わずかなステップで黄色と青色もカラートラッキングの対象に含めることが出来ます
2022-04-08 カメラ仮調整
2022-04-08 回り込みとショートブレーキの仕様変更
2022-04-08 PD制御調整
2022-04-08 グローバル変数と定数の置き場所を変更
2022-04-08 LCDがエラー情報を吐くように変更
2022-04-16 PIDパラメータ確定
2022-04-16 回り込み大雑把だけど確定
2022-04-16 色の閾値仮決め
2022-04-16 けいはんな機ソフトウェアの骨組み的なところ組んだ
2022-04-17 ピン番号とLCD表示位置の仮決め
2022-04-21 新造機向けにファーム書き換え
2022-04-21 USBシリアルを追加
2022-04-21 新ライブラリのインストール
2022-04-22 新造機向けファーム改造(カメラの値の出方が左右逆になっている現象に対処)
2022-04-22 なんかよくわからん(VSCodeが勝手に変更しやがった)
2022-04-22 使わないライブラリの消去
2022-04-22 なんやねんコイツ
2022-04-22 プログラムの最適化と新規オフセット値の適用
2022-04-23 大会中変更1(マキシマムモード()実装と回り込みの3分割化)
2022-04-28 READMEにコードとライセンスに関する内容を追記
2022-04-29 ジャパンで実装したところ全て
2022-05-08 Teensy 4.0の動作周波数OC環境の追加
2022-05-08 ジャパンオープンけいはんな2022ベースで外部からの無線通信による操作に対応
2022-05-08 眠ってたM5StickCちゃんを供養しようの会
2022-05-08 無線機、格ゲーコントローラーver
2022-05-08 無線機、ジョイコントローラー的なやつで操縦するver
2022-05-08 M5StickCの電圧を確認するためだけのやつ
2022-05-08 電圧状況に応じて文字色が変わるよ
2022-05-30 Update README.md
    スペルミス訂正
2022-07-20 文字の色変わる仕様、やっぱりなしの方向で
2022-07-20 表示色を白で統一
2022-07-20 色々細かくバグ取り(バグ取り)
2022-07-20 GyroController用受信側Picoのプログラム
2022-07-20 PS3コントローラーとPicoを接続して自律機を無線機化するプロジェクトから生まれた何か
2023-03-31 VSCodeからのテストコミット
